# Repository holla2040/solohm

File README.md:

solohm
======

Open Source Solar Panel Electronic Load

This project is a hardware/firmware design to aid in testing of solar panels. solohm is powered from the panel's output and an off-the-shelf lipo battery, it can load the panel at its maximum power point, WiFi UDP broadcast current and voltage readings packets, perform IV curve sweeps and measure many temperatures at different panel locations. 

SolOhm replaces bulky expensive, AC-powered, non-waterproof, non-high-temperature rated, multi-unit, wired-communication test equipment with a single unit that's inexpensive, panel-powered, waterproof, industrial temperature rated, and wireless. The goal is 5 minute install: bolt SolOhm to your frame, connect your panel's + and - connectors, attach temperature probes and start testing.  

Specifications
<ul>
<li>Input voltage - 50VDC maximum</li>
<li>Input current - 10A maximum, fused</li>
<li>Input power - 300W maximum</li>
<li>Operating temperature - &lt; 130F, acquisition electronics TEC cooled</li>
<li>Display - OLED graphic display</li>
<li>User interface - IR remote DirectTV RC65X or Sony TV</li> 
<li>MPPT tracking - periodic sweep, perturb/observe, manual</li>
<li>Mechanical - frame/poll attachment, IP63, extruded aluminium, glass/plexiglass, passive heatsink</li>
<li>IV sweep time - &lt; 1 sec, VOC to ISC, 500 samples, Vpanel@ISC < 0.25V@8A<li>
<li>ADC resolution - 12 bit, 4096 steps full scale</li>
<li>Temperature probes - DS18B20, COTS stainless steel, multi-drop, +/-0.5C over -10C to +85C</li>
<li>Power supply - COTS 3S LIPO battery, panel powered charger, 24 hour operation</li>
<li>Data transmission - UDP broadcast and control, HTTP REST</li>
<li>Data collection - micro SD slot</li>
<li>Timestamp - UTC via NTP source with battery-backed real time clock</li>
<li>Firmware - OTA updates (planned)</li>
<li>Calibration - Requires 40V@10A power supply, precision voltmeter and ammeter</li>

</ul>

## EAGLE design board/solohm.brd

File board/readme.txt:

This information, board files, assembly instructions and bill of
materials is company confidental.
Not for distribution.

board
    solohm

version
    0.1

description
    Top layer:                  pcbname.GTL
    Bottom layer:               pcbname.GBL
    Solder Stop Mask top:       pcbname.GTS
    Solder Stop Mask Bottom:    pcbname.GBS
    Silk Top:                   pcbname.GTO
    Silk Bottom:                pcbname.GBO
    NC Drill:                   pcbname.TXT

    drd drill data
    dri drill info
    gpi gerber info
    readme.txt info, has fudicial info

fudicials at
    0.25,0.1
    3.6,3.8

layer stack up sequence
    top     x.GTL
    bottom  x.GBL

contact info
    Craig Hollabaugh
    970 690 4911
    craig@hollabaugh.com

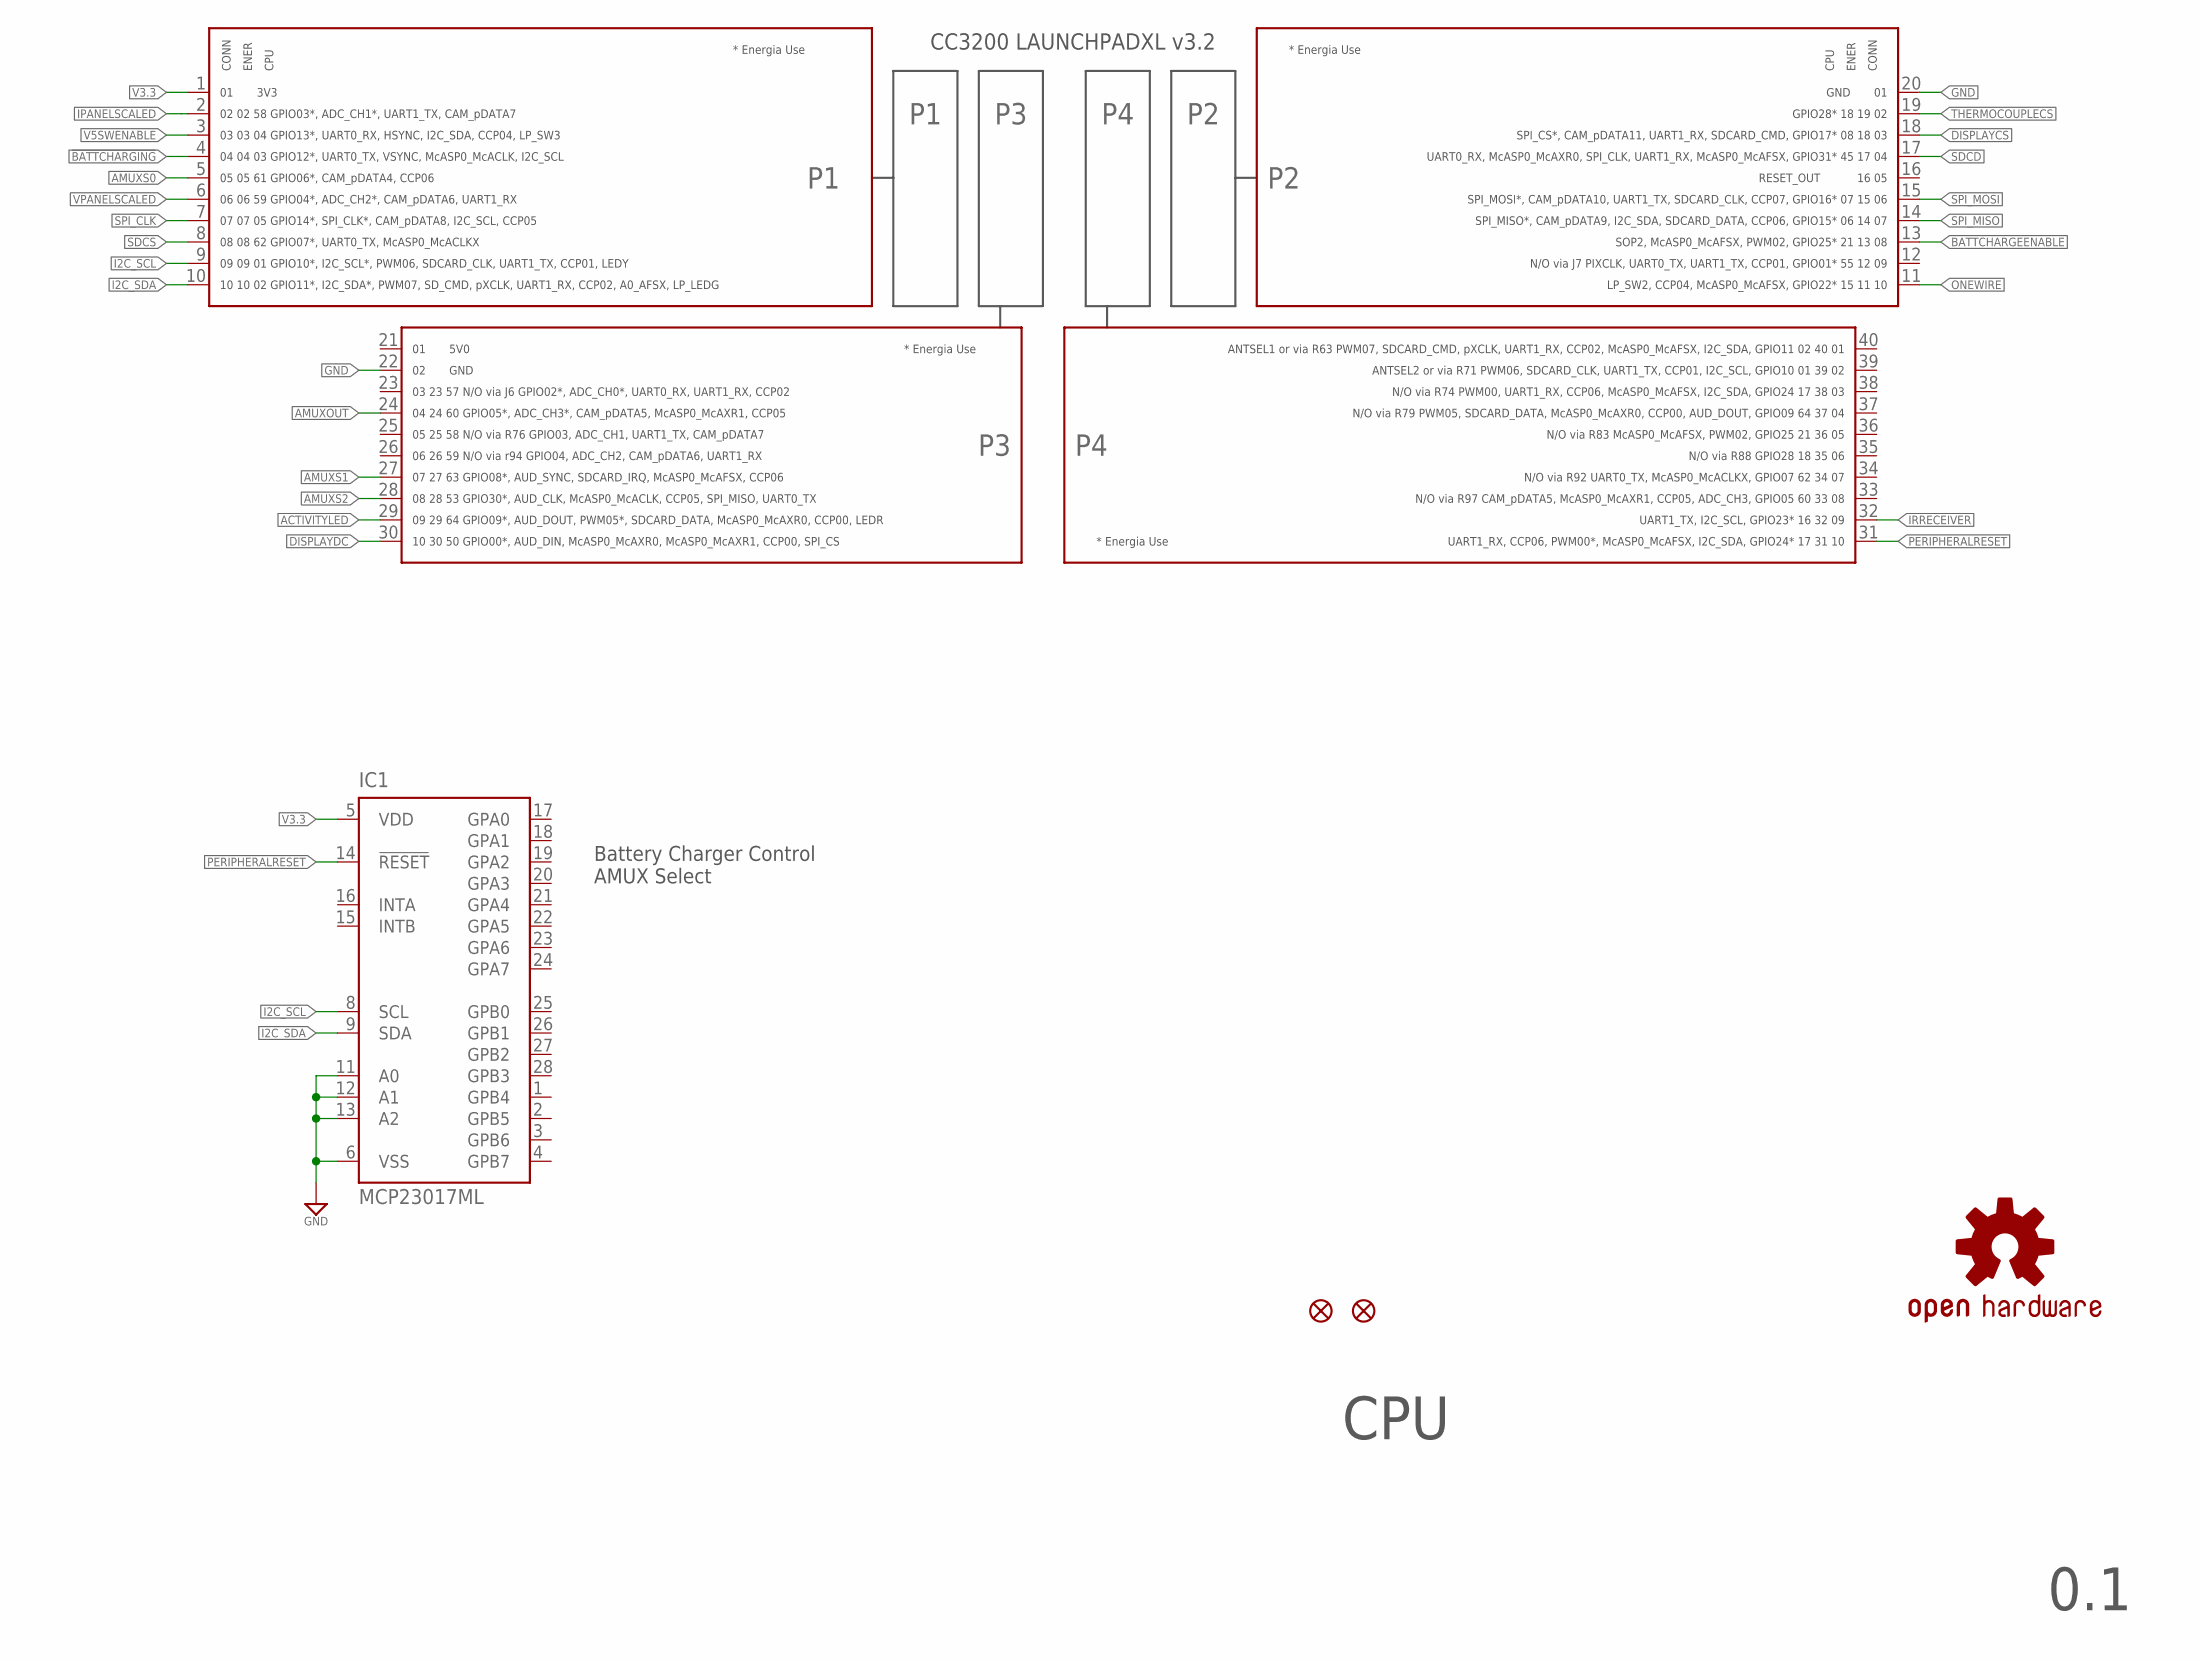
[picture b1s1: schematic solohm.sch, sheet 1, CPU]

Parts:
A1: CC3200-LAUNCHXL-BOOSTERPACK
IC1: MCP23017ML; QFN28-ML_6X6MM
JP1, JP2: FIDUCIALUFIDUCIAL; MICRO-FIDUCIAL
LOGO1: LOGO-OSHWL; LOGO-OSHW-L

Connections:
!BATTCHARGING: A1.4; also elsewhere on the board
ACTIVITYLED: A1.29; also elsewhere on the board
AMUXOUT: A1.24; also elsewhere on the board
AMUXS0: A1.5; also elsewhere on the board
AMUXS1: A1.27; also elsewhere on the board
AMUXS2: A1.28; also elsewhere on the board
BATTCHARGEENABLE: A1.13; also elsewhere on the board
DISPLAYCS: A1.18; also elsewhere on the board
DISPLAYDC: A1.30; also elsewhere on the board
GND: A1.20, A1.22, IC1.6 (VSS), IC1.11 (A0), IC1.12 (A1), IC1.13 (A2); also elsewhere on the board
I2C_SCL: A1.9, IC1.8 (SCL); also elsewhere on the board
I2C_SDA: A1.10, IC1.9 (SDA); also elsewhere on the board
IPANELSCALED: A1.2; also elsewhere on the board
IRRECEIVER: A1.32; also elsewhere on the board
ONEWIRE: A1.11; also elsewhere on the board
PERIPHERALRESET: A1.31, IC1.14 (!RESET); also elsewhere on the board
SDCD: A1.17; also elsewhere on the board
SDCS: A1.8; also elsewhere on the board
SPI_CLK: A1.7; also elsewhere on the board
SPI_MISO: A1.14; also elsewhere on the board
SPI_MOSI: A1.15; also elsewhere on the board
THERMOCOUPLECS: A1.19; also elsewhere on the board
V3.3: A1.1, IC1.5 (VDD); also elsewhere on the board
V5SWENABLE: A1.3; also elsewhere on the board
VPANELSCALED: A1.6; also elsewhere on the board

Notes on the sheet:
CPU
0.1
Battery Charger Control AMUX Select

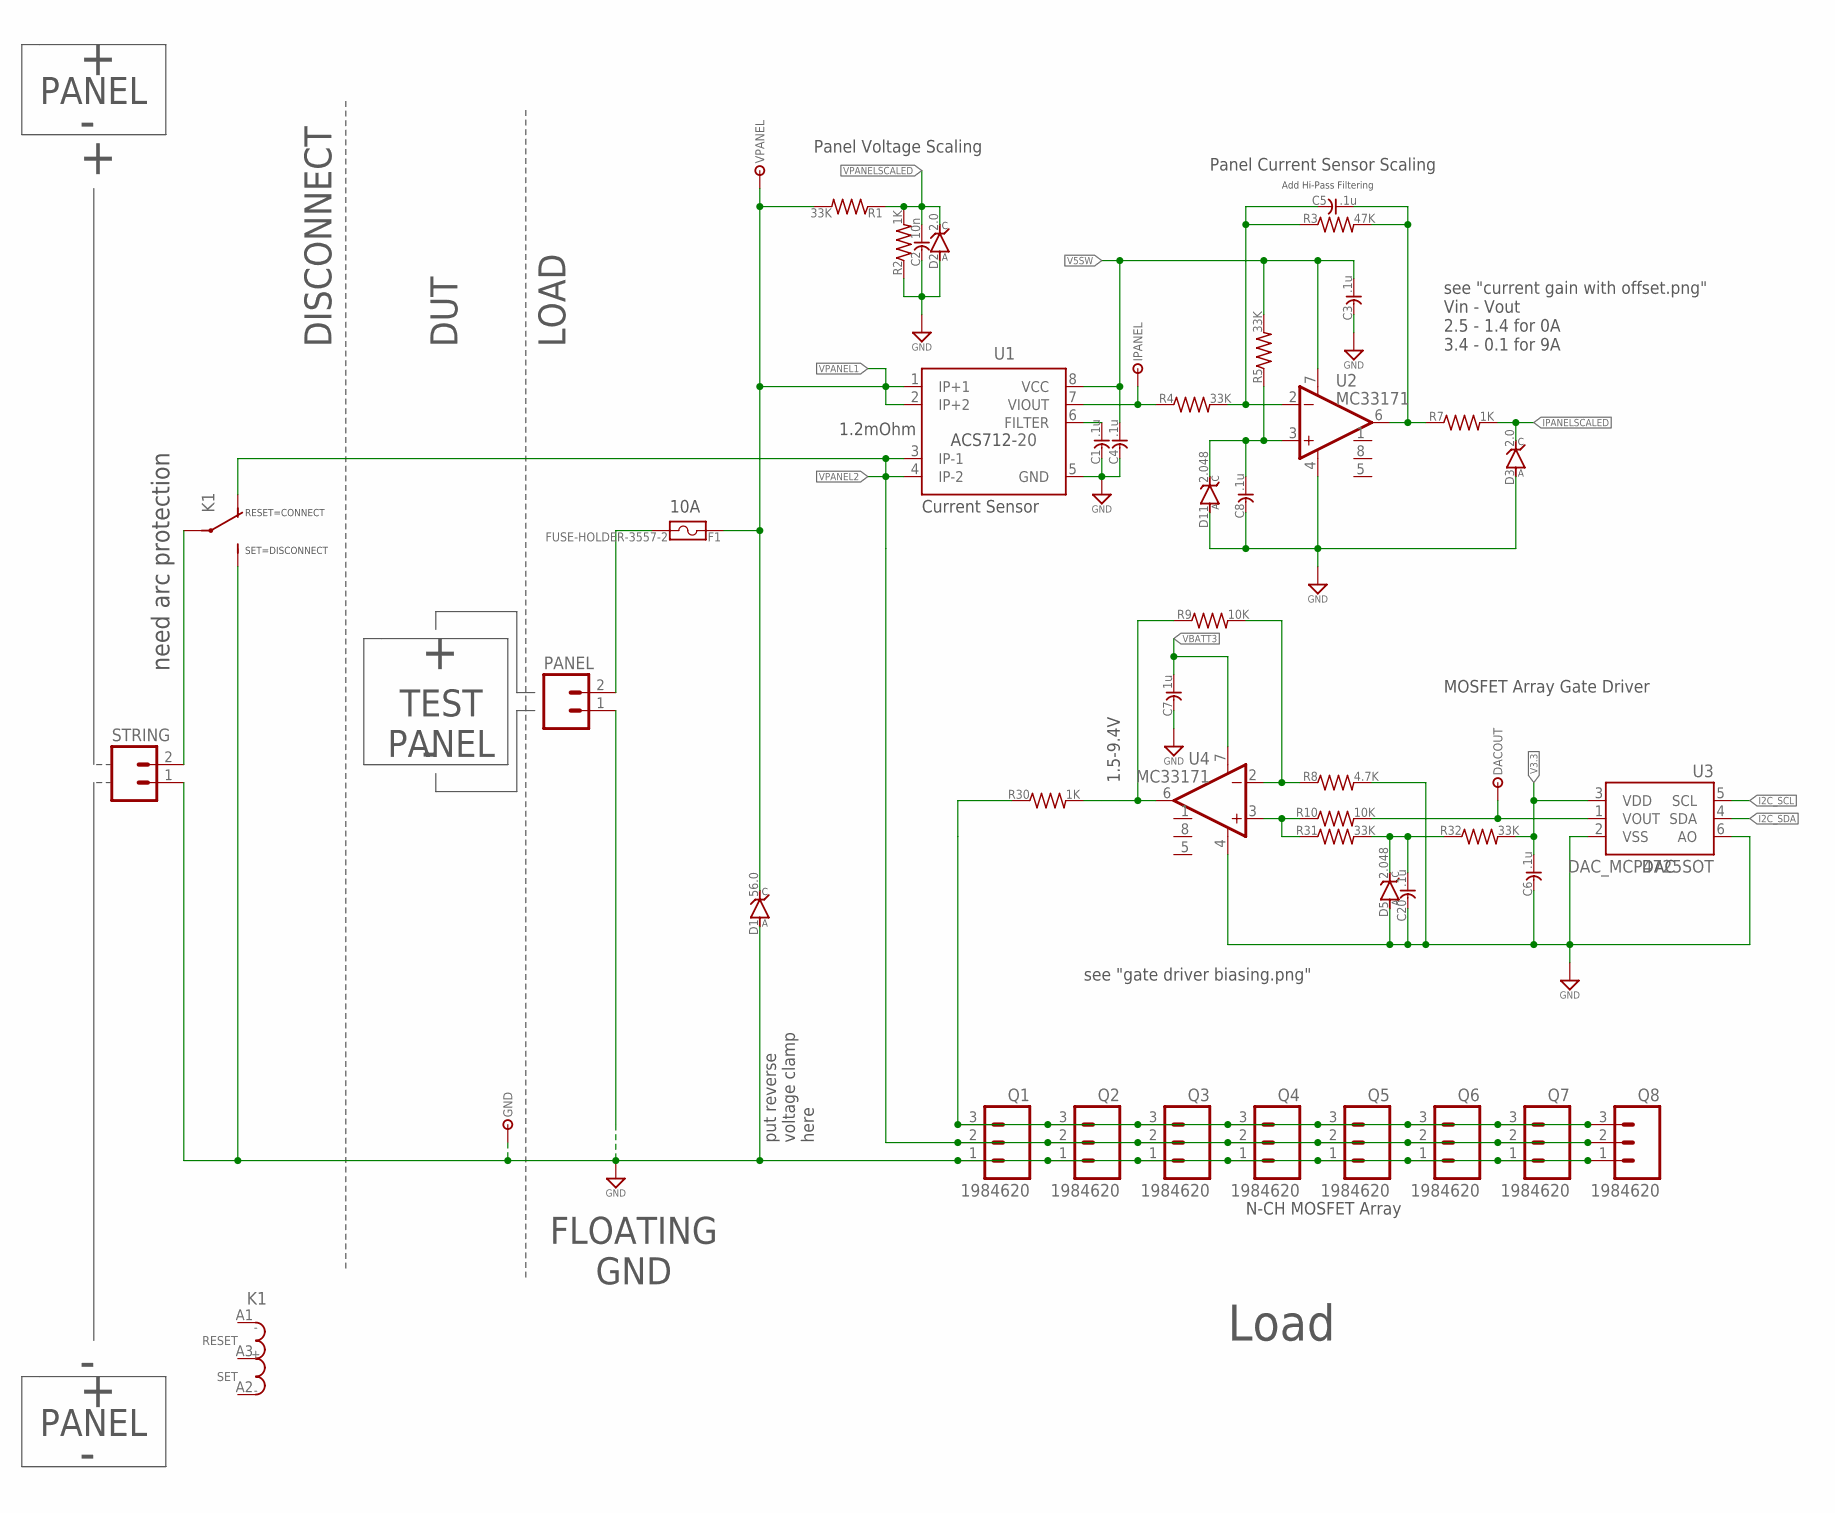
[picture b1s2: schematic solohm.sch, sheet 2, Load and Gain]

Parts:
C1, C3, C4, C5, C6, C8, C20: .1u; C0603
C2: 10n; C0603
C7: 1u; C0603
D1: 56.0; SOD-323
D2, D3: 2.0; SOD-323
D5, D11: 2.048; SOT23-3
DACOUT: TESTPOINTTHRU; TPTHRU
F1: FUSE-HOLDER-3557-2; 3557-2
GND: TESTPOINTTHRU; TPTHRU
IPANEL: TESTPOINTTHRU; TPTHRU
K1: RELAY-LATCHING-DUAL-1FORMC-5MM-16A; RELAY-1FORMC-5MM-16A
PANEL: M02-6.35MM; OSTT702
Q1, Q2, Q3, Q4, Q5, Q6, Q7, Q8: 1984620
R1, R4, R5, R31, R32: 33K; R0603
R2, R7, R30: 1K; R0603
R3: 47K; R0603
R8: 4.7K; R0603
R9, R10: 10K; R0603
STRING: M02-6.35MM; OSTT702
U1: 20; SOIC08
U2, U4: MC33171; SO08
U3: DAC_MCP4725SOT; SOT23-6
VPANEL: TESTPOINTTHRU; TPTHRU

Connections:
GATES: Q1.3, Q2.3, Q3.3, Q4.3, Q5.3, Q6.3, Q7.3, Q8.3, R30.1
GND: C1.2, C2.2, C3.2, C4.2, C6.2, C7.2, C8.2, C20.2, D1.A, D2.A, D3.A, D5.2 (A), D11.2 (A), GND.1, K1.14@1 (NO), K1.14@2 (NO), PANEL.1, Q1.1, Q2.1, Q3.1, Q4.1, Q5.1, Q6.1, Q7.1, Q8.1, R2.1, R8.2, STRING.1, U1.5 (GND), U2.4 (V-), U3.2 (VSS), U3.6 (AO), U4.4 (V-); also elsewhere on the board
I2C_SCL: U3.5 (SCL); also elsewhere on the board
I2C_SDA: U3.4 (SDA); also elsewhere on the board
IPANELSCALED: D3.C, R7.2; also elsewhere on the board
unnamed: R9.1, R30.2, U4.6 (OUT)
unnamed: C20.1, D5.1 (C), R31.2, R32.1
unnamed: C1.1, U1.6 (FILTER)
unnamed: IPANEL.1, R4.1, U1.7 (VIOUT)
unnamed: C5.2, R3.1, R4.2, U2.2 (IN-)
unnamed: C8.1, D11.1 (C), R5.1, U2.3 (IN+)
unnamed: C5.1, R3.2, R7.1, U2.6 (OUT)
unnamed: DACOUT.1, R10.2, U3.1 (VOUT)
unnamed: R8.1, R9.2, U4.2 (IN-)
unnamed: R10.1, R31.1, U4.3 (IN+)
unnamed: K1.11@1 (W), K1.11@2 (W), STRING.2
V3.3: C6.1, R32.2, U3.3 (VDD); also elsewhere on the board
V5SW: C3.1, C4.1, R5.2, U1.8 (VCC), U2.7 (V+); also elsewhere on the board
VBATT3: C7.1, U4.7 (V+); also elsewhere on the board
VPANEL0: F1.2@1, F1.2@2, PANEL.2
VPANEL1: D1.C, F1.1@1, F1.1@2, R1.2, U1.1 (IP+1), U1.2 (IP+2), VPANEL.1
VPANEL2: K1.12@1 (NC), K1.12@2 (NC), Q1.2, Q2.2, Q3.2, Q4.2, Q5.2, Q6.2, Q7.2, Q8.2, U1.3 (IP-1), U1.4 (IP-2); also elsewhere on the board
VPANELSCALED: C2.1, D2.C, R1.1, R2.2; also elsewhere on the board

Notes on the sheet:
Load
Add Hi-Pass Filtering
see "gate driver biasing.png"
1.5-9.4V
see "current gain with offset.png" Vin - Vout 2.5 - 1.4 for 0A 3.4 - 0.1 for 9A
10A
DAC
PANEL
LOAD
DISCONNECT
TEST PANEL
FLOATING GND
need arc protection
Current Sensor
1.2mOhm
Panel Current Sensor Scaling
MOSFET Array Gate Driver
N-CH MOSFET Array
DUT
Panel Voltage Scaling
put reverse voltage clamp here
SET=DISCONNECT
RESET=CONNECT

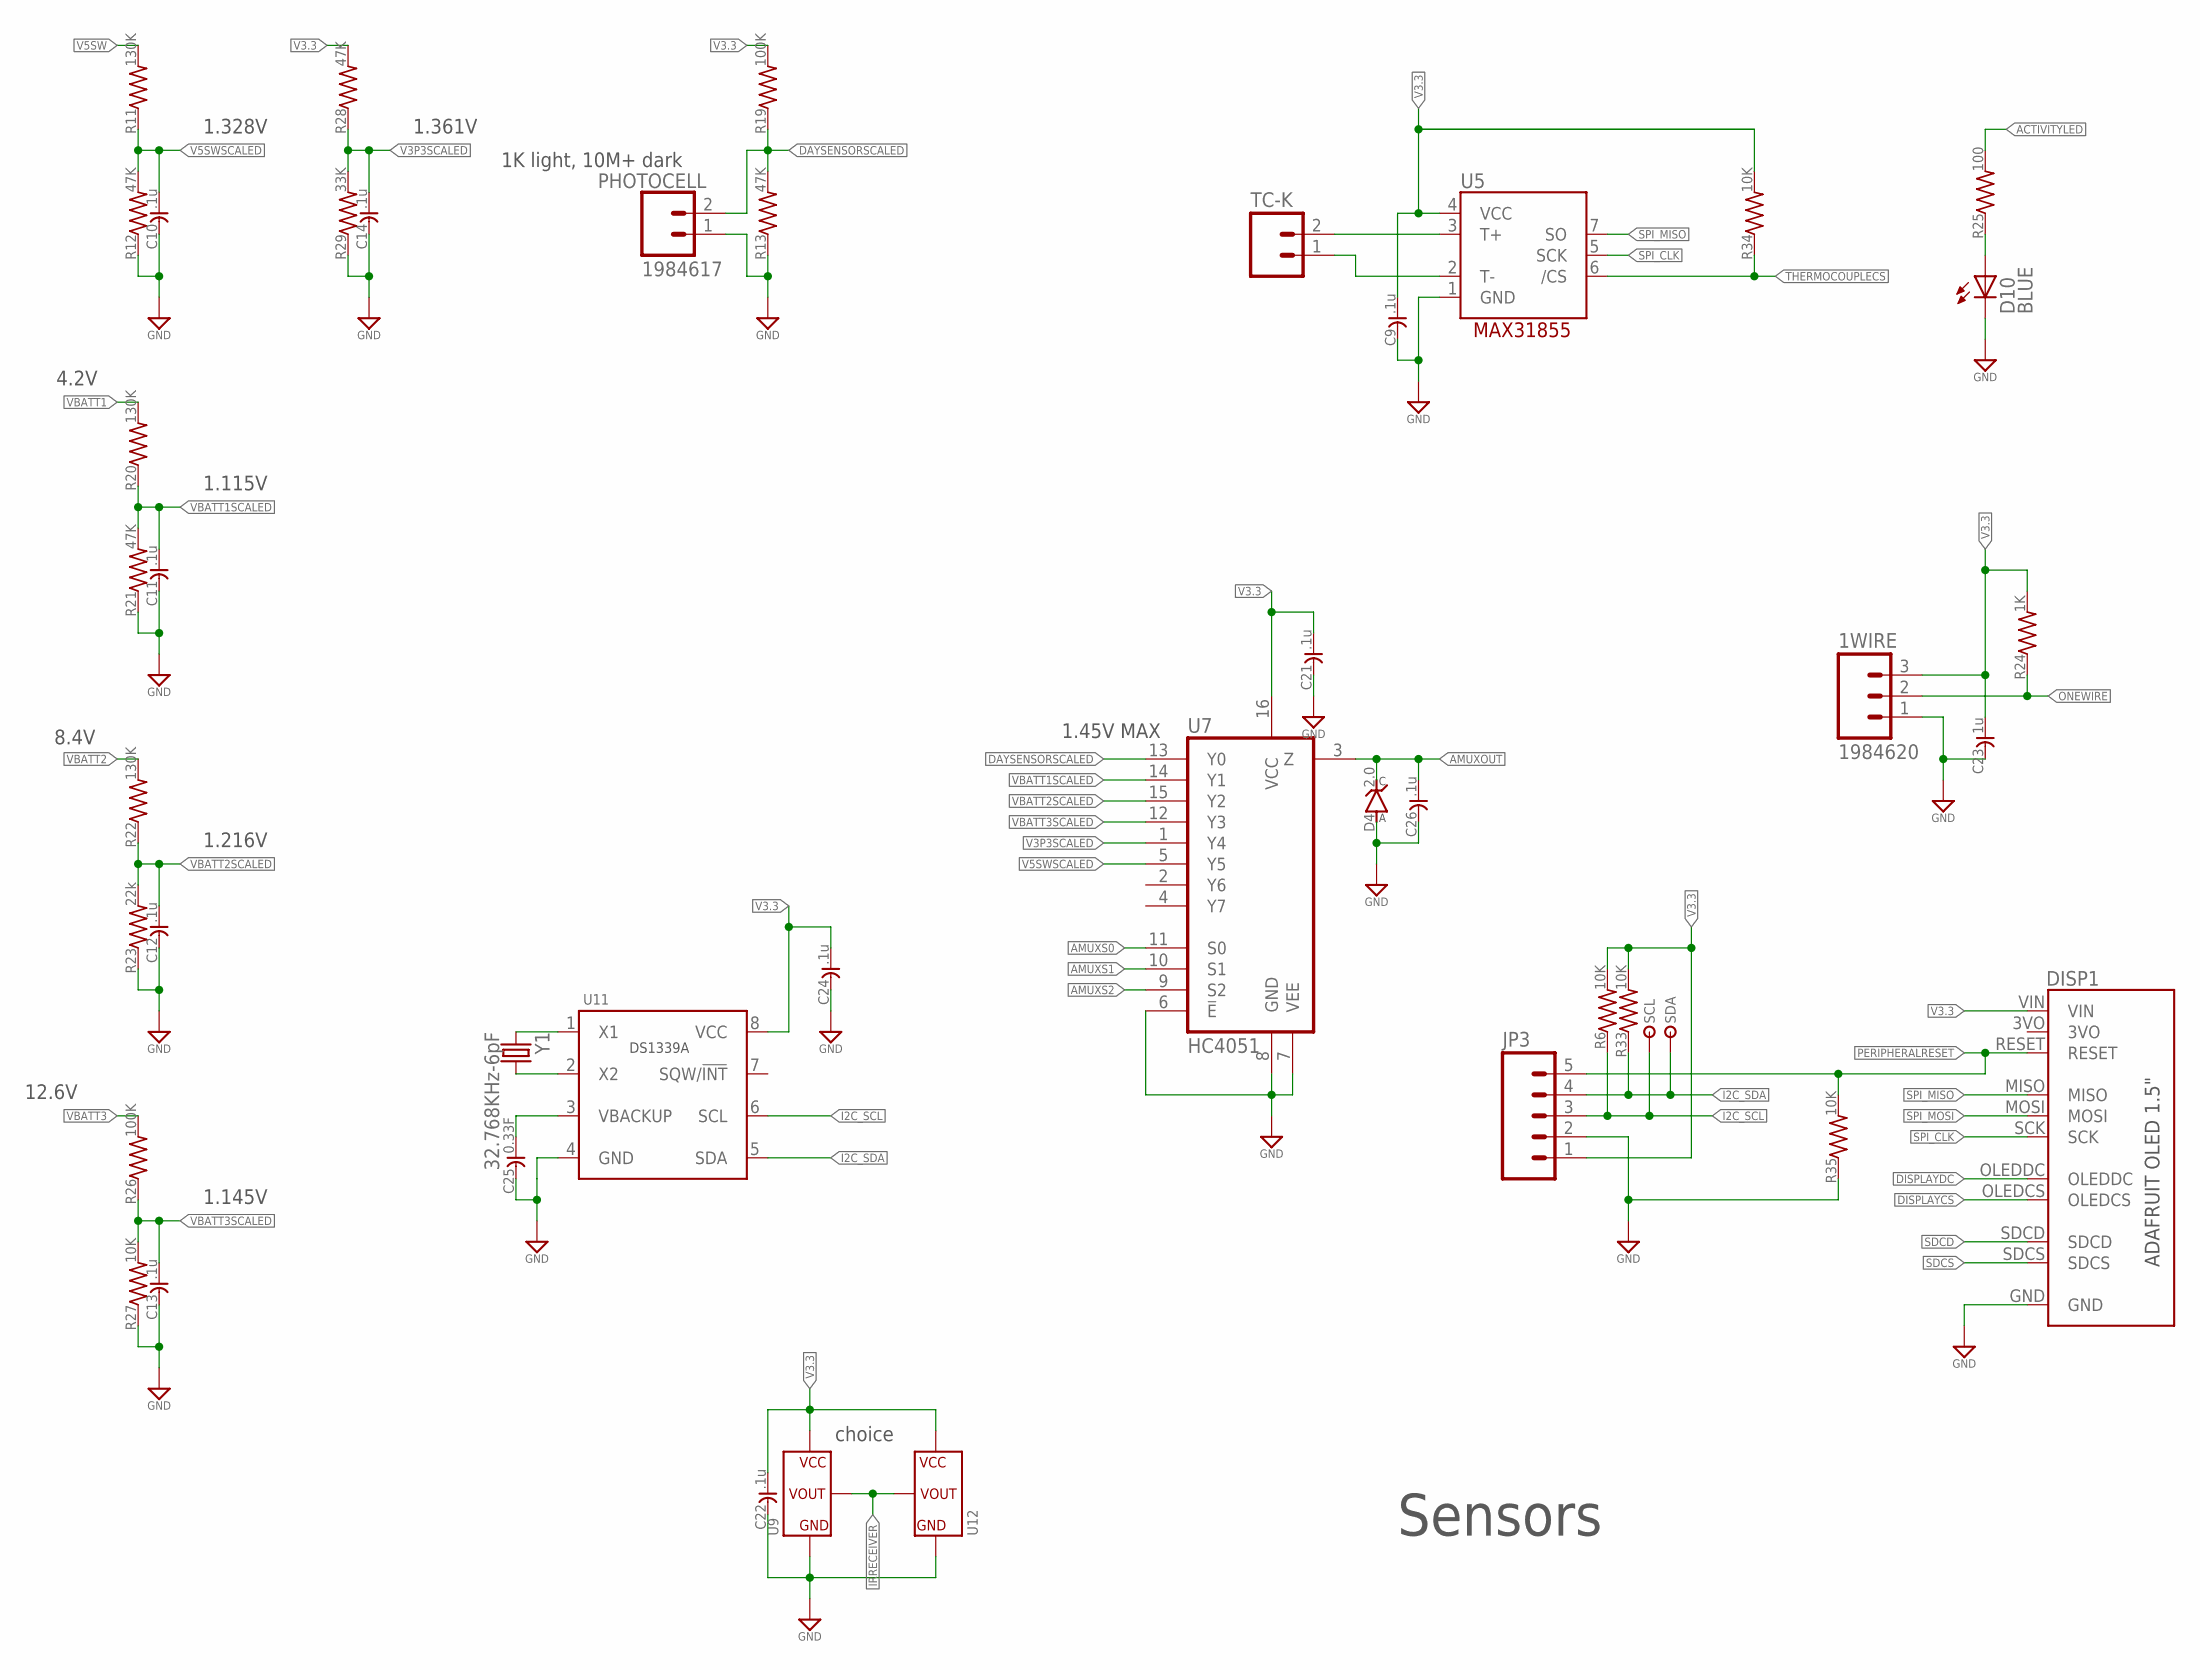
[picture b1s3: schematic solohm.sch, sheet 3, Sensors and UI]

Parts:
1WIRE: 1984620
C9, C10, C11, C12, C13, C14, C21, C22, C24, C26: .1u; C0603
C23: 1u; C0603
C25: 0.33F; CAP-SUPER-AXIAL-10MM
D4: 2.0; SOD-323
D10: BLUE; LED0805
DISP1: BOARD-DISP-ADAFRUIT-OLED-1.5
JP3: M05PTH; 1X05
PHOTOCELL: 1984617
R6, R27, R33, R34, R35: 10K; R0603
R11, R20, R22: 130K; R0603
R12, R13, R21, R28: 47K; R0603
R19, R26: 100K; R0603
R23: 22k; R0603
R24: 1K; R0603
R25: 100; R0603
R29: 33K; R0603
SCL: TESTPOINTTHRU; TPTHRU
SDA: TESTPOINTTHRU; TPTHRU
TC-K: M02-1984617; 1984617
U5: THERMOCOUPLE-MAX31855; SO08
U7: HC4051; SO16
U9: IRDETECTOR-THRU
U11: RTC-DS1339A; MSOP8
U12: IRDETECTOR-TSOP6X
Y1: 32.768KHz-6pF; ABS25

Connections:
ACTIVITYLED: R25.2; also elsewhere on the board
AMUXOUT: C26.1, D4.C, U7.3 (Z); also elsewhere on the board
AMUXS0: U7.11 (S0); also elsewhere on the board
AMUXS1: U7.10 (S1); also elsewhere on the board
AMUXS2: U7.9 (S2); also elsewhere on the board
DAYSENSORSCALED: PHOTOCELL.2, R13.2, R19.1, U7.13 (Y0)
DISPLAYCS: DISP1.OLEDCS; also elsewhere on the board
DISPLAYDC: DISP1.OLEDDC; also elsewhere on the board
GND: 1WIRE.1, C9.2, C10.2, C11.2, C12.2, C13.2, C14.2, C21.2, C22.2, C23.2, C24.2, C25.- (2), C26.2, D4.A, D10.C, DISP1.GND, JP3.2, PHOTOCELL.1, R12.1, R13.1, R21.1, R23.1, R27.1, R29.1, R35.1, U5.1 (GND), U7.6 (!E), U7.7 (VEE), U7.8 (GND), U9.GND, U11.4 (GND), U12.GND; also elsewhere on the board
I2C_SCL: JP3.3, R6.1, SCL.1, U11.6 (SCL); also elsewhere on the board
I2C_SDA: JP3.4, R33.1, SDA.1, U11.5 (SDA); also elsewhere on the board
IRRECEIVER: U9.VOUT, U12.OUT (VOUT); also elsewhere on the board
unnamed: TC-K.2, U5.3 (T+)
unnamed: TC-K.1, U5.2 (T-)
unnamed: U11.1 (X1), Y1.1
unnamed: U11.2 (X2), Y1.4 (2)
unnamed: C25.+ (1), U11.3 (VBACKUP)
unnamed: D10.A, R25.1
ONEWIRE: 1WIRE.2, R24.1; also elsewhere on the board
PERIPHERALRESET: DISP1.RESET, JP3.5, R35.2; also elsewhere on the board
SDCD: DISP1.SDCD; also elsewhere on the board
SDCS: DISP1.SDCS; also elsewhere on the board
SPI_CLK: DISP1.SCK, U5.5 (SCK); also elsewhere on the board
SPI_MISO: DISP1.MISO, U5.7 (SO); also elsewhere on the board
SPI_MOSI: DISP1.MOSI; also elsewhere on the board
THERMOCOUPLECS: R34.1, U5.6 (/CS); also elsewhere on the board
V3.3: 1WIRE.3, C9.1, C21.1, C22.1, C23.1, C24.1, DISP1.VIN, JP3.1, R6.2, R19.2, R24.2, R28.2, R33.2, R34.2, U5.4 (VCC), U7.16 (VCC), U9.VCC, U11.8 (VCC), U12.VCC; also elsewhere on the board
V3P3SCALED: C14.1, R28.1, R29.2, U7.1 (Y4)
V5SW: R11.2; also elsewhere on the board
V5SWSCALED: C10.1, R11.1, R12.2, U7.5 (Y5)
VBATT1: R20.2; also elsewhere on the board
VBATT1SCALED: C11.1, R20.1, R21.2, U7.14 (Y1)
VBATT2: R22.2; also elsewhere on the board
VBATT2SCALED: C12.1, R22.1, R23.2, U7.15 (Y2)
VBATT3: R26.2; also elsewhere on the board
VBATT3SCALED: C13.1, R26.1, R27.2, U7.12 (Y3)

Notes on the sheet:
Sensors
1K light, 10M+ dark
1.45V MAX
4.2V
8.4V
12.6V
1.328V
1.115V
1.216V
1.145V
1.361V
choice

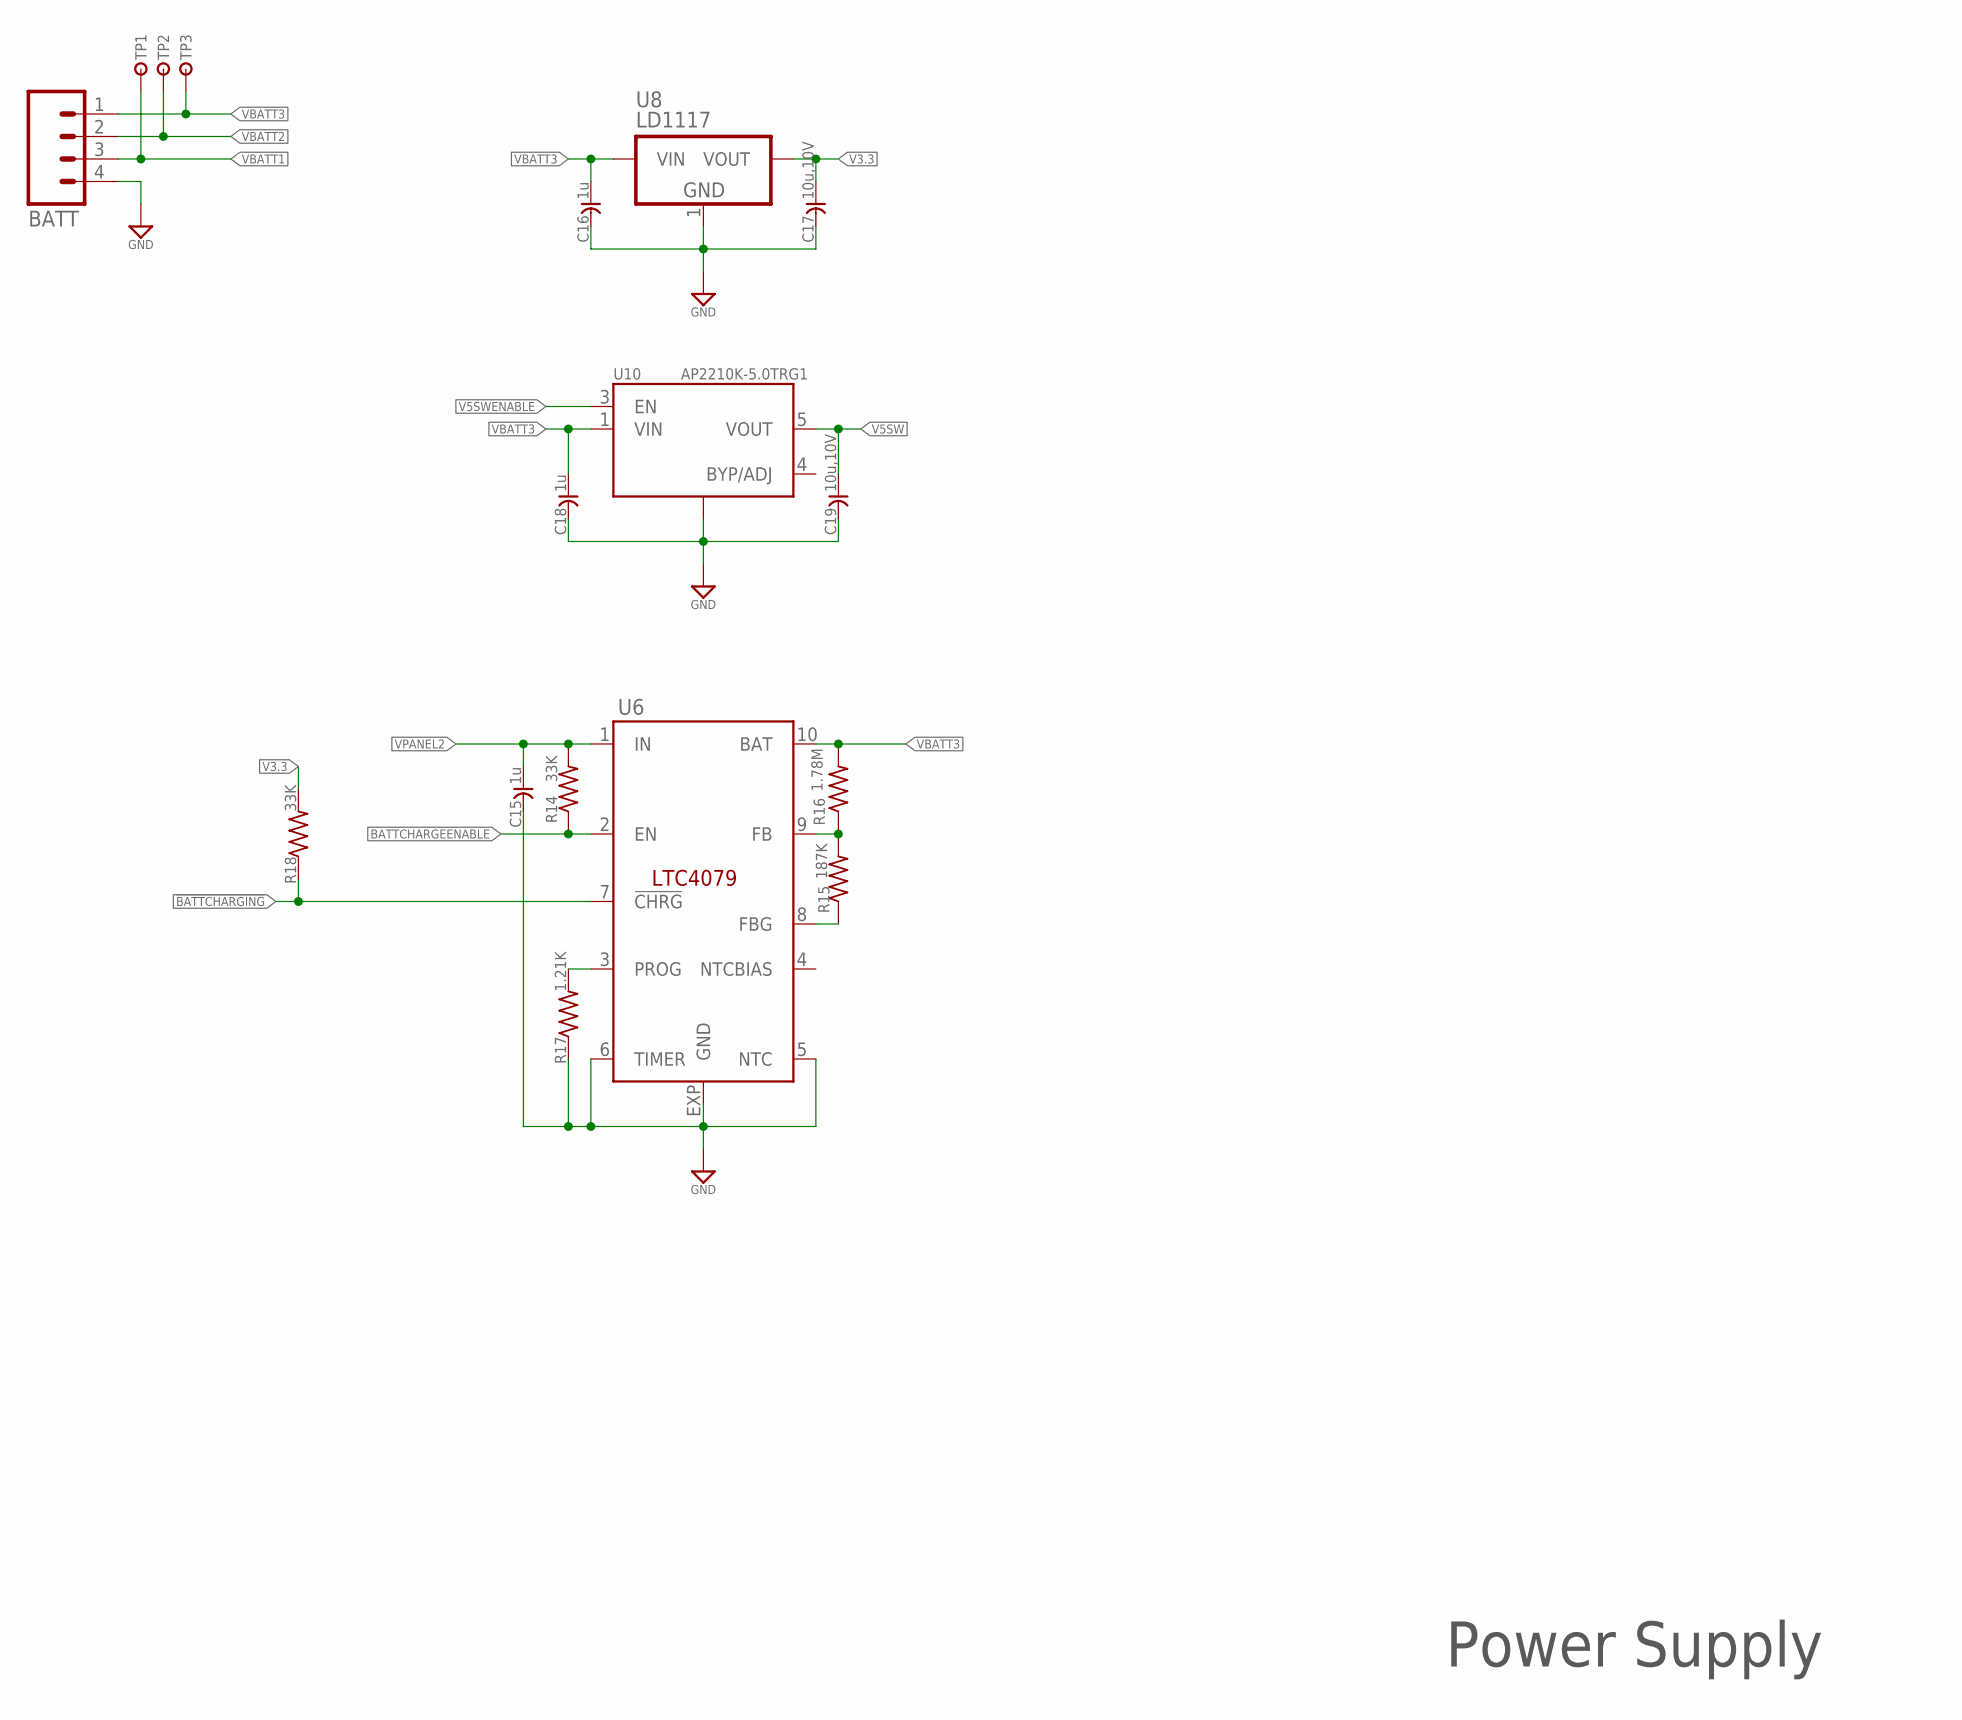
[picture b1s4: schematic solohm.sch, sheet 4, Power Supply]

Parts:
BATT: M04-B4B-XH-VERT; JST-B4B-XH-VERT
C15, C16, C18: 1u; C0603
C17, C19: 10u,10V; C0805
R14, R18: 33K; R0603
R15: 187K; R0603
R16: 1.78M; R0603
R17: 1.21K; R0603
TP1, TP2, TP3: TESTPOINT0.5; TP0.5R
U6: BATTCHARGER-LTC4079; DFN10-3X3
U8: LD1117; SOT-223
U10: AP2210K-5.0TRG1; SOT23-5

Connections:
!BATTCHARGING: R18.1, U6.7 (!CHRG); also elsewhere on the board
BATTCHARGEENABLE: R14.1, U6.2 (EN); also elsewhere on the board
GND: BATT.4, C15.2, C16.2, C17.2, C18.2, C19.2, R17.1, U6.5 (NTC), U6.6 (TIMER), U6.EXP (GND), U8.1 (GND), U10.2 (GND); also elsewhere on the board
unnamed: R15.2, R16.1, U6.9 (FB)
unnamed: R15.1, U6.8 (FBG)
unnamed: R17.2, U6.3 (PROG)
V3.3: C17.1, R18.2, U8.2 (VOUT); also elsewhere on the board
V5SW: C19.1, U10.5 (VOUT); also elsewhere on the board
V5SWENABLE: U10.3 (EN); also elsewhere on the board
VBATT1: BATT.3, TP1.TP; also elsewhere on the board
VBATT2: BATT.2, TP2.TP; also elsewhere on the board
VBATT3: BATT.1, C16.1, C18.1, R16.2, TP3.TP, U6.10 (BAT), U8.3 (VIN), U10.1 (VIN); also elsewhere on the board
VPANEL2: C15.1, R14.2, U6.1 (IN); also elsewhere on the board

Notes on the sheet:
Power Supply

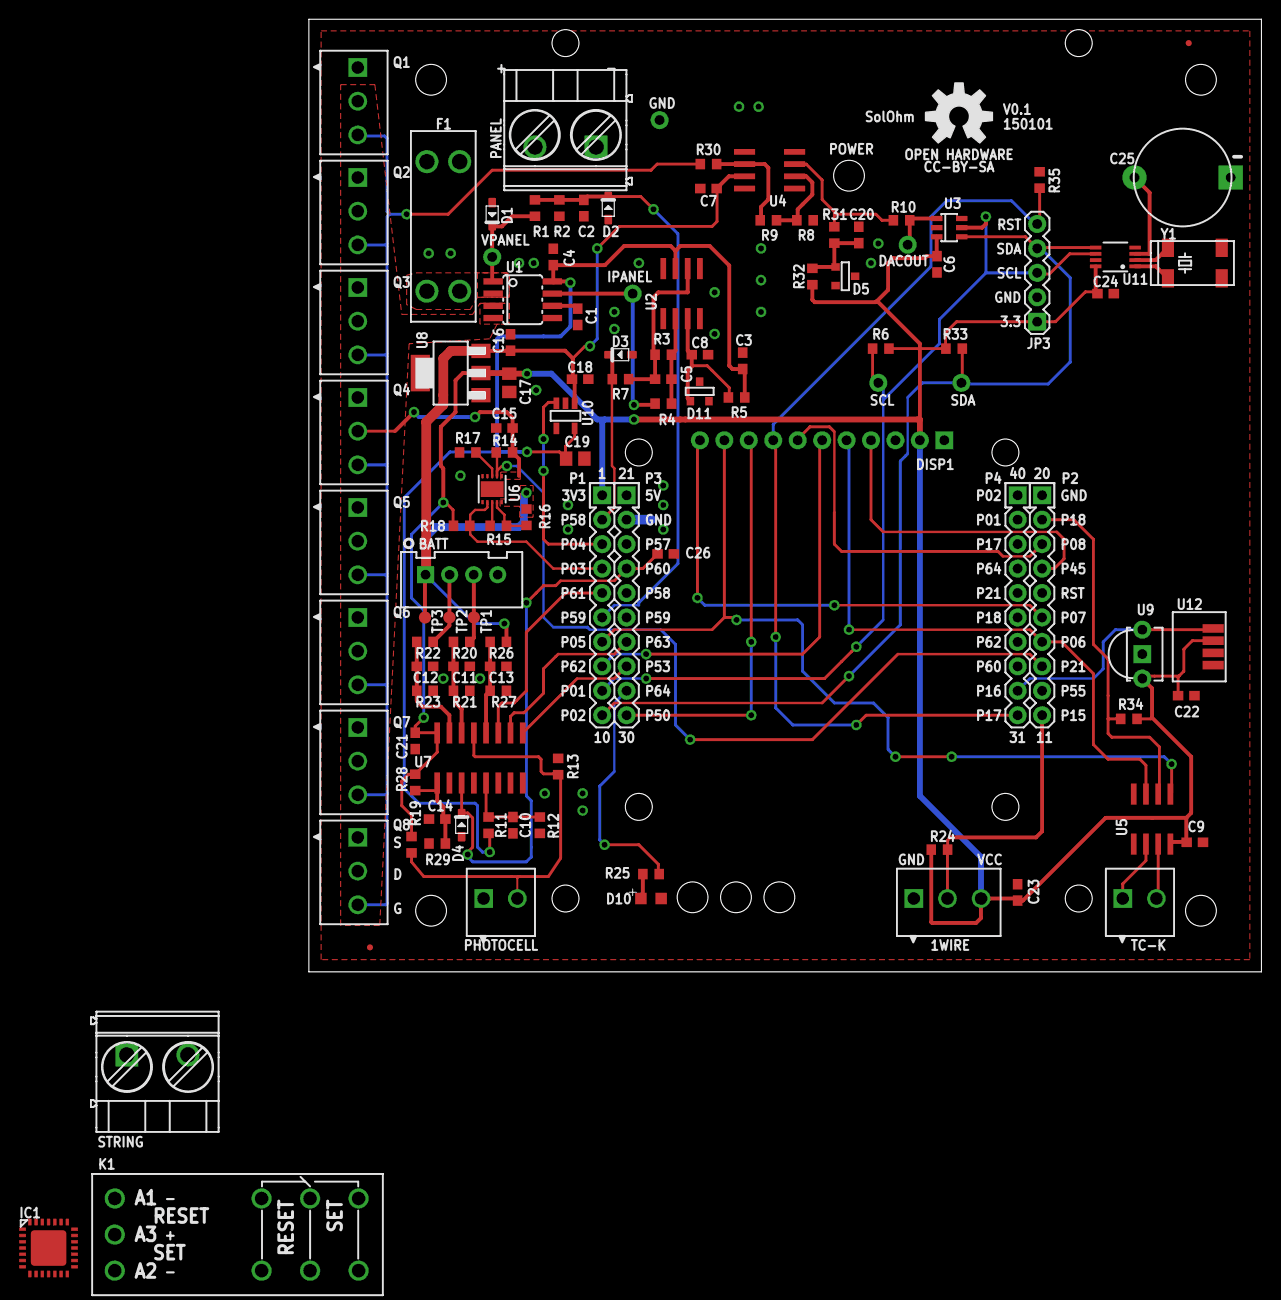
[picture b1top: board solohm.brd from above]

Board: 2 copper layers, 99.0 x 99.0 mm, 113 parts (0 on the bottom side), 59 nets.

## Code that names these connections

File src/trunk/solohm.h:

#ifndef SOLOHM_H
#define SOLOHM_H 1

#define VPANELSCALED    A2
#define IPANELSCALED    A1

#define V5SWENABLE      03

#define AMUXS0          05
#define AMUXS1          27
#define AMUXS2          28
#define AMUXOUT         A3

enum {
    DAYSENSORSCALED,
    VBATT1SCALED,
    VBATT2SCALED,
    VBATT3SCALED,
    V3P3SCALED,
    V5SWSCALED
};

#define ACTIVITYLED     29

#define THERMOCOUPLECS  19

#define IRRECEIVER      32

#define DISPLAYDC       30
#define DISPLAYCS       18
#define DISPLAYRESET    31

#define SDCD            17
#define SDCS            08

#define SPI_MOSI        15
#define SPI_MISO        14
#define SPI_CLK         07

#define I2C_SCL         09
#define I2C_SDA         10

#define BATTCHARGING     04
#define BATTCHARGEENABLE 13

#endif

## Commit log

2015-01-03 initial add
2015-01-05 here's the v0.1 hardware version, sent this to board house for fab
2015-01-09 changed top silk char width
2015-01-11 added disconnect for operation in string
2015-01-11 recreated
2015-01-12 added dual-coil latching relay and 23017 I/O port for future battery charger control
2015-01-13 fixed a bunch of top silk errors here and there
2015-01-13 just tweaking things from v0.1 board problems
2015-01-20 initial add for src little tweaks to the board added lines to board design notes file
2015-01-22 fixed amux ground islands ino has functional vbatt sensing
2015-01-22 added VPANEL and IPANEL value calculation
2015-01-26 added more notes created testing data from MOSFET/heatsink temperature testing bs/solohm_dac now is keyboard driven bs/rtc functional
2015-01-26 cleaned up photo
2015-01-26 re-org some files started solohm class from babysteps
2015-01-26 removing this file, its in the lib dir now
2015-01-26 solohm app add adc, dac and udp to SolOhm class, now broadcasts on 8380
2015-01-27 moved these notes and todo to github issues
2015-01-30 added http server
2015-01-31 tcp and http support added started working on struct based file system for html, etc
2015-01-31 added loadsweep and chart
2015-01-31 added mode, rload now reporting individual battery voltages and 'vbatt'(all in series)
2015-02-01 added dual axis plots reduced dac range of interest
2015-02-01 added loadmppt, loadoff, loadup, loaddown support added DAC to dashboard
2015-02-01 added ppanel support removed the faulty dac offset, need better approach
2015-09-21 dir reorg
2015-09-21 now transparent png
2015-09-21 iinitial add

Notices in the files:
parts and their libraries:
holla: CC-BY-SA
